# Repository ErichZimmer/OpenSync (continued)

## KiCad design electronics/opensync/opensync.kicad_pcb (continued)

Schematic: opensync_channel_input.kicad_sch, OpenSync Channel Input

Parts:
C65: 100n; C_0402_1005Metric_small_pads; voltage 50V; tolerance ±10%; manufacturer_pn CGA2B3X7R1H104KT0Y0F; LCSC C343042
D1: ESD701DPYR; X1SON-2_L1.0-W0.6-P0.65-BI; MPN ESD701DPYR; LCSC Part C42409125
J17: 705530001; CONN_705530001_02_MOL; LCSC C564143
R81: 1k; R_0402_1005Metric; tolerance ±1%; voltage 50V; manufacturer_pn CRCW04021K00FKEDHP; LCSC C313354
R82: 10k; R_0402_1005Metric; tolerance ±1%; voltage 50V; manufacturer_pn CRCW040210K0FKED; LCSC C71617
U18: TLV3601DCKR; SC-70-5_L2.0-W1.3-P0.65-LS2.1-BR; MPN TLV3601DCKR; LCSC C2974371

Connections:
+3V3: C65.1, U18.5 (VCC); also elsewhere on the board
/Input Channels/Input Channel 1/SIG_LOGIC: U18.3 (IN+); also elsewhere on the board
/Input Channels/SIG_TRIG: U18.1 (OUT); also elsewhere on the board
GND: C65.2, D1.2, J17.2, R81.2, U18.2 (VEE); also elsewhere on the board
unnamed: D1.1, J17.1, R82.2
unnamed: R81.1, R82.1, U18.4 (IN-)

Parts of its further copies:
C66: 100n; C_0402_1005Metric_small_pads; voltage 50V; tolerance ±10%; manufacturer_pn CGA2B3X7R1H104KT0Y0F; LCSC C343042
D11: ESD701DPYR; X1SON-2_L1.0-W0.6-P0.65-BI; MPN ESD701DPYR; LCSC Part C42409125
J18: 705530001; CONN_705530001_02_MOL; LCSC C564143
R83: 1k; R_0402_1005Metric; tolerance ±1%; voltage 50V; manufacturer_pn CRCW04021K00FKEDHP; LCSC C313354
R84: 10k; R_0402_1005Metric; tolerance ±1%; voltage 50V; manufacturer_pn CRCW040210K0FKED; LCSC C71617
U19: TLV3601DCKR; SC-70-5_L2.0-W1.3-P0.65-LS2.1-BR; MPN TLV3601DCKR; LCSC C2974371

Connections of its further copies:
+3V3: C66.1, U19.5 (VCC); also elsewhere on the board
/Input Channels/Input Channel 2/SIG_LOGIC: U19.3 (IN+); also elsewhere on the board
/Input Channels/SIG_GATE: U19.1 (OUT); also elsewhere on the board
GND: C66.2, D11.2, J18.2, R83.2, U19.2 (VEE); also elsewhere on the board
unnamed: D11.1, J18.1, R84.2
unnamed: R83.1, R84.1, U19.4 (IN-)

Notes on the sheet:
NOTE MICROCONTROLLER SCHEM. HAS GPIO PULL DOWNN

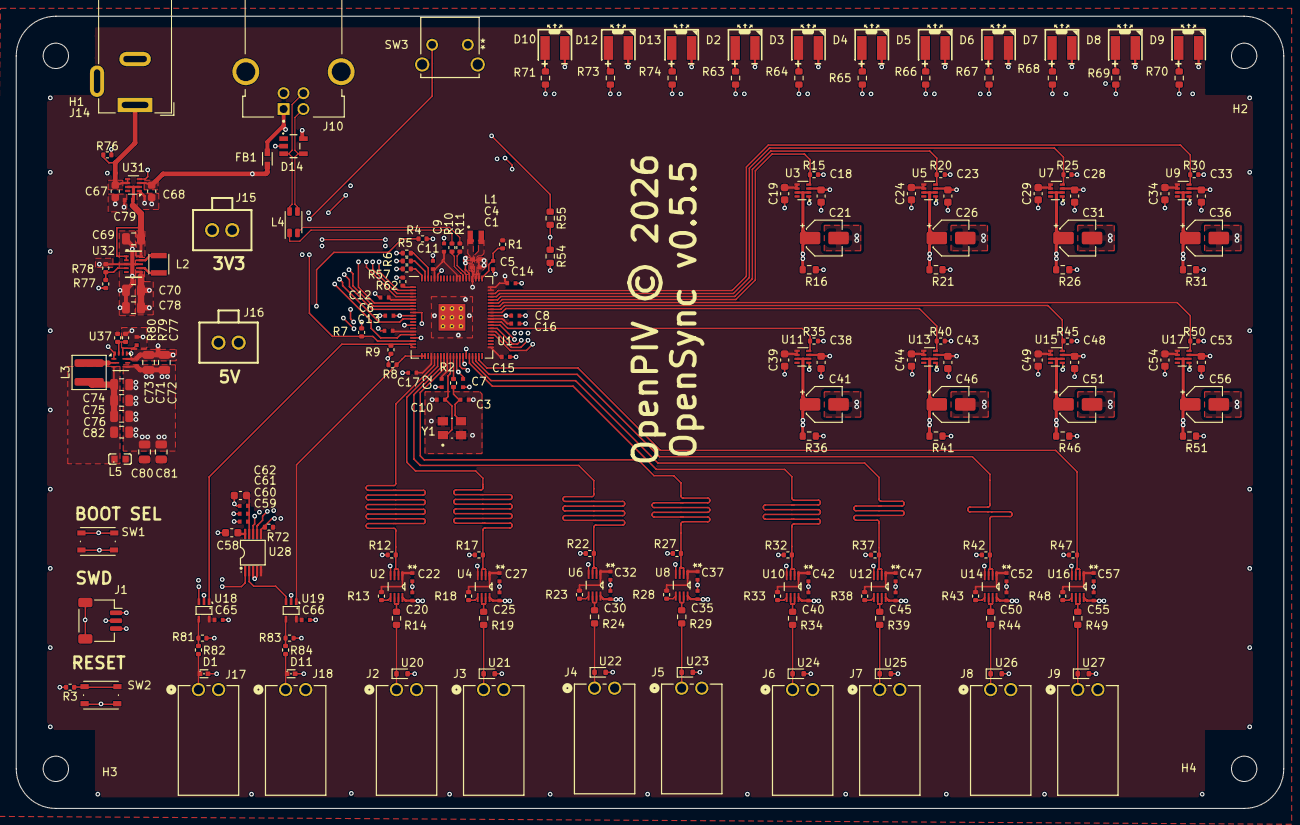
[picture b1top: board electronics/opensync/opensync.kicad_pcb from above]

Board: 4 copper layers, 160.0 x 100.0 mm, 230 parts (0 on the bottom side), 120 nets.

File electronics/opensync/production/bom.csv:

Designator,Footprint,Quantity,Value,LCSC Part #
"C1, C4, C5",0402,3,4.7u,C342983
"C10, C11, C12, C13, C14, C15, C16, C17, C20, C22, C25, C27, C30, C32, C35, C37, C40, C42, C45, C47, C50, C52, C55, C57, C6, C61, C65, C66, C7, C79, C8, C9",0402,32,100n,C343042
"C18, C19, C23, C24, C28, C29, C33, C34, C38, C39, C43, C44, C48, C49, C53, C54, C58, C62, C67, C68",0603,20,1u,C76708
"C2, C3",0402,2,15p,C338103
"C21, C26, C31, C36, C41, C46, C51, C56",CP_Elec_4x5.4,8,22u,C2164097
C59,0402,1,100p,C281750
C60,0402,1,1n,C76704
"C69, C70, C74, C75, C76, C78, C80, C81, C82",0805,9,22u,C342717
"C71, C72",0805,2,10u,C342722
C73,0402,1,2.2n,C338081
C77,0402,1,470n,C432936
"D1, D11",X1SON-2_L1.0-W0.6-P0.65-BI,2,ESD701DPYR,C42409125
"D10, D12, D13, D2, D3, D4, D5, D6, D7, D8, D9",LED-SMD_L4.0-W3.6_A67F-U2BA-1-3A4B-30-R33,11,LED,C7545687
D14,WE-TVS_SOT23-5L,1,5V,C5341668
FB1,FB_Wurth_WE-CBF-0603_W2.6,1,0603_W2.6_742792641,C2649308
J1,JST_SH_SM03B-SRSS-TB_1x03-1MP_P1.00mm_Horizontal,1,SM03B-SRSS-TB,C160403
J10,AMPHENOL_61729-0010BLF,1,61729-0010BLF,C598579
J14,BarrelJack_Wuerth_6941xx301002,1,Barrel_Jack_Switch,C5441017
"J15, J16",CONN-TH_705430001,2,Conn_01x02,C127361
"J17, J18, J2, J3, J4, J5, J6, J7, J8, J9",CONN_705530001_02_MOL,10,705530001,C564143
L1,L_pol_2016,1,3.3u,C42411119
L2,L_TDK_TMS252012ALM,1,470n,C24296304
L3,L_Wuerth_MAPI-4020,1,2.2u,C5521727
L4,L_CommonMode_Wurth_WE-CNSW-1206,1,Choke_Wurth_WE-CNSW_744232090,C2649327
L5,L0603,1,7427922808,C2661810
R1,0402,1,33,C844506
"R10, R11",0402,2,27,C4162575
"R12, R15, R17, R20, R22, R25, R27, R30, R32, R35, R37, R40, R42, R45, R47, R5, R50, R57, R6, R62, R7, R72, R8, R82, R84, R9",0402,26,10k,C71617
"R13, R18, R23, R28, R33, R38, R43, R48",0402,8,47k,C482184
"R14, R19, R24, R29, R34, R39, R44, R49",0603,8,39,C544038
"R16, R21, R26, R31, R36, R41, R46, R51, R54",0603,9,10k,C844918
"R2, R3, R4, R81, R83",0402,5,1k,C313354
R55,0603,1,5.6k,C844799
"R63, R64, R65, R66, R67, R68, R69, R70, R71, R73, R74",0603,11,470,C844786
R76,0402,1,100k,C481918
R77,0402,1,806k,C2076627
R78,0402,1,91k,C2086333
R79,0402,1,4.99k,C4010684
R80,0402,1,15.6k,C2075329
"SW1, SW2",SW_Push_1P1T_NO_Vertical_Wuerth_434133025816,2,SW_Push,C5504987
SW3,SW2_1825027-G_TEC,1,2-1825027-0,C590206
U1,RP2350-QFN-80-1EP_10x10_P0.4mm_EP3.4x3.4mm_ThermalVias,1,RP2354_80QFN,C39843328
"U10, U12, U14, U16, U2, U4, U6, U8",DCU8,8,SN74LVC2T45DCUR,C15741
"U11, U13, U15, U17, U3, U31, U5, U7, U9",SOT-583-8,9,TPS2116DRL,C3235557
"U18, U19",SC-70-5_L2.0-W1.3-P0.65-LS2.1-BR,2,TLV3601DCKR,C2974371
"U20, U21, U22, U23, U24, U25, U26, U27",D_SOD-523,8,TPD1E05U06DYA,C3702980
U28,VSSOP-10_L3.0-W3.0-P0.50-LS4.9-BL,1,DAC8563SDGSR,C1554729
U32,DLA0010A,1,TPS63802DLAR,C2845237
U37,Texas_RPU0010A_VQFN-HR-10_2x2mm_P0.5mm,1,TPS62912,C3198056
Y1,XTAL_ABM8-272-T3,1,ABM8-272-T3,C20625731

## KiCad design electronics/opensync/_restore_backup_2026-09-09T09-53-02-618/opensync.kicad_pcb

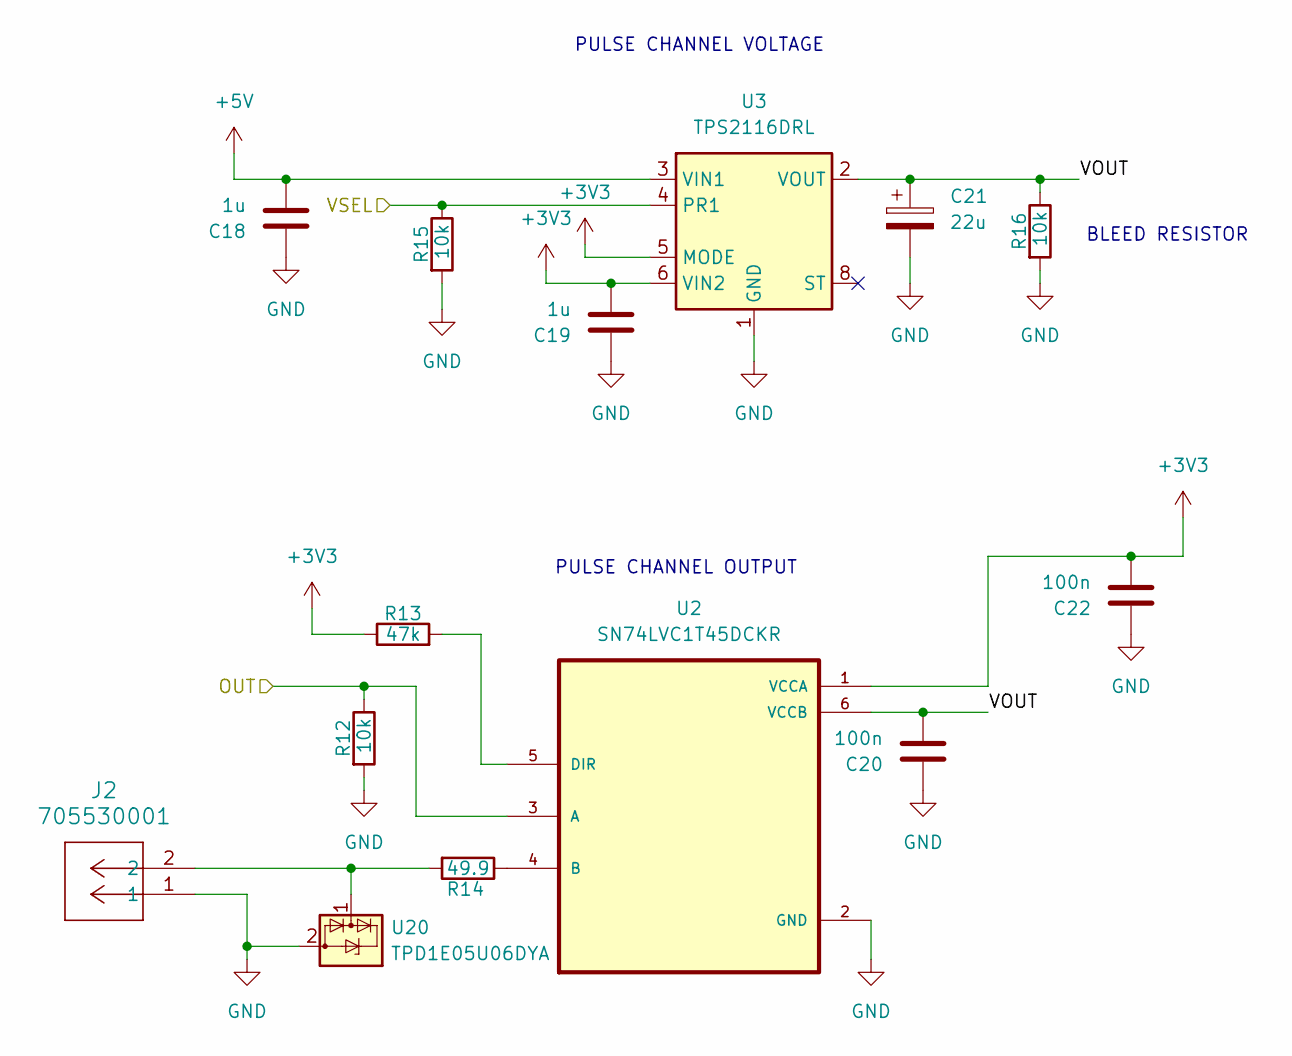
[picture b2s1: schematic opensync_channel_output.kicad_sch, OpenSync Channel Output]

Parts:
C18, C19: 1u; C_0402_1005Metric_small_pads
C20, C22: 100n; C_0402_1005Metric_small_pads; LCSC C60474
C21: 22u; CP_Elec_4x5.4
J2: 705530001; CONN_705530001_02_MOL; LCSC C564143
R12, R15: 10k; R_0402_1005Metric; LCSC C71617
R13: 47k; R_0402_1005Metric; LCSC C176117
R14: 49.9; R_0603_1608Metric; LCSC C1858992
R16: 10k; R_0402_1005Metric
U2: SN74LVC1T45DCKR; SOT65P210X110-6N; LCSC C9382
U3: TPS2116DRL; SOT-583-8
U20: TPD1E05U06DYA; D_SOD-523

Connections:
+3V3: C19.2, C22.2, R13.1, U2.1 (VCCA), U3.5 (MODE), U3.6 (VIN2); also elsewhere on the board
+5V: C18.2, U3.3 (VIN1); also elsewhere on the board
/OUT_A: R12.1, U2.3 (A); also elsewhere on the board
/Output Channel 1/VOUT: C20.2, C21.1, R16.1, U2.6 (VCCB), U3.2 (VOUT), U3.7 (VOUT)
/VSEL_A: R15.1, U3.4 (PR1); also elsewhere on the board
GND: C18.1, C19.1, C20.1, C21.2, C22.1, J2.1, R12.2, R15.2, R16.2, U2.2 (GND), U3.1 (GND), U20.2 (GND); also elsewhere on the board
unnamed: R14.1, U2.4 (B)
unnamed: R13.2, U2.5 (DIR)
unnamed: J2.2, R14.2, U20.1 (I/O)

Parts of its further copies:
C23, C24, C28, C29, C33, C34, C38, C39, C43, C44, C48, C49, C53, C54, C58, C59: 1u; C_0402_1005Metric_small_pads
C25, C27, C30, C32, C35, C37, C40, C42, C45, C47, C50, C52, C55, C57, C60, C62: 100n; C_0402_1005Metric_small_pads; LCSC C60474
C26, C31, C36, C41, C46, C51, C56, C61: 22u; CP_Elec_4x5.4
J3, J4, J5, J6, J7, J8, J9, J10: 705530001; CONN_705530001_02_MOL; LCSC C564143
R17, R20, R22, R25, R27, R30, R32, R35, R37, R40, R42, R45, R47, R50, R52, R55: 10k; R_0402_1005Metric; LCSC C71617
R18, R23, R28, R33, R38, R43, R48, R53: 47k; R_0402_1005Metric; LCSC C176117
R19, R24, R29, R34, R39, R44, R49, R54: 49.9; R_0603_1608Metric; LCSC C1858992
R21, R26, R31, R36, R41, R46, R51, R56: 10k; R_0402_1005Metric
U4, U6, U8, U10, U12, U14, U16, U18: SN74LVC1T45DCKR; SOT65P210X110-6N; LCSC C9382
U5, U7, U9, U11, U13, U15, U17, U19: TPS2116DRL; SOT-583-8
U21, U22, U23, U24, U25, U26, U27, U28: TPD1E05U06DYA; D_SOD-523

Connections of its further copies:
+3V3: C24.2, C27.2, C29.2, C32.2, C34.2, C37.2, C39.2, C42.2, C44.2, C47.2, C49.2, C52.2, C54.2, C57.2, C59.2, C62.2, R18.1, R23.1, R28.1, R33.1, R38.1, R43.1, R48.1, R53.1, U4.1 (VCCA), U5.5 (MODE), U5.6 (VIN2), U6.1 (VCCA), U7.5 (MODE), U7.6 (VIN2), U8.1 (VCCA), U9.5 (MODE), U9.6 (VIN2), U10.1 (VCCA), U11.5 (MODE), U11.6 (VIN2), U12.1 (VCCA), U13.5 (MODE), U13.6 (VIN2), U14.1 (VCCA), U15.5 (MODE), U15.6 (VIN2), U16.1 (VCCA), U17.5 (MODE), U17.6 (VIN2), U18.1 (VCCA), U19.5 (MODE), U19.6 (VIN2); also elsewhere on the board
+5V: C23.2, C28.2, C33.2, C38.2, C43.2, C48.2, C53.2, C58.2, U5.3 (VIN1), U7.3 (VIN1), U9.3 (VIN1), U11.3 (VIN1), U13.3 (VIN1), U15.3 (VIN1), U17.3 (VIN1), U19.3 (VIN1); also elsewhere on the board
/OUT_B: R17.1, U4.3 (A); also elsewhere on the board
/OUT_C: R22.1, U6.3 (A); also elsewhere on the board
/OUT_D: R27.1, U8.3 (A); also elsewhere on the board
/OUT_E: R32.1, U10.3 (A); also elsewhere on the board
/OUT_F: R37.1, U12.3 (A); also elsewhere on the board
/OUT_G: R42.1, U14.3 (A); also elsewhere on the board
/OUT_H: R47.1, U16.3 (A); also elsewhere on the board
/OUT_T0: R52.1, U18.3 (A); also elsewhere on the board
/Output Channel 2/VOUT: C25.2, C26.1, R21.1, U4.6 (VCCB), U5.2 (VOUT), U5.7 (VOUT)
/Output Channel 3/VOUT: C30.2, C31.1, R26.1, U6.6 (VCCB), U7.2 (VOUT), U7.7 (VOUT)
/Output Channel 4/VOUT: C35.2, C36.1, R31.1, U8.6 (VCCB), U9.2 (VOUT), U9.7 (VOUT)
/Output Channel 5/VOUT: C40.2, C41.1, R36.1, U10.6 (VCCB), U11.2 (VOUT), U11.7 (VOUT)
/Output Channel 6/VOUT: C45.2, C46.1, R41.1, U12.6 (VCCB), U13.2 (VOUT), U13.7 (VOUT)
/Output Channel 7/VOUT: C50.2, C51.1, R46.1, U14.6 (VCCB), U15.2 (VOUT), U15.7 (VOUT)
/Output Channel 8/VOUT: C55.2, C56.1, R51.1, U16.6 (VCCB), U17.2 (VOUT), U17.7 (VOUT)
/Output Channel T0/VOUT: C60.2, C61.1, R56.1, U18.6 (VCCB), U19.2 (VOUT), U19.7 (VOUT)
/VSEL_B: R20.1, U5.4 (PR1); also elsewhere on the board
/VSEL_C: R25.1, U7.4 (PR1); also elsewhere on the board
/VSEL_D: R30.1, U9.4 (PR1); also elsewhere on the board
/VSEL_E: R35.1, U11.4 (PR1); also elsewhere on the board
/VSEL_F: R40.1, U13.4 (PR1); also elsewhere on the board
/VSEL_G: R45.1, U15.4 (PR1); also elsewhere on the board
/VSEL_H: R50.1, U17.4 (PR1); also elsewhere on the board
/VSEL_T0: R55.1, U19.4 (PR1); also elsewhere on the board
GND: C23.1, C24.1, C25.1, C26.2, C27.1, C28.1, C29.1, C30.1, C31.2, C32.1, C33.1, C34.1, C35.1, C36.2, C37.1, C38.1, C39.1, C40.1, C41.2, C42.1, C43.1, C44.1, C45.1, C46.2, C47.1, C48.1, C49.1, C50.1, C51.2, C52.1, C53.1, C54.1, C55.1, C56.2, C57.1, C58.1, C59.1, C60.1, C61.2, C62.1, J3.1, J4.1, J5.1, J6.1, J7.1, J8.1, J9.1, J10.1, R17.2, R20.2, R21.2, R22.2, R25.2, R26.2, R27.2, R30.2, R31.2, R32.2, R35.2, R36.2, R37.2, R40.2, R41.2, R42.2, R45.2, R46.2, R47.2, R50.2, R51.2, R52.2, R55.2, R56.2, U4.2 (GND), U5.1 (GND), U6.2 (GND), U7.1 (GND), U8.2 (GND), U9.1 (GND), U10.2 (GND), U11.1 (GND), U12.2 (GND), U13.1 (GND), U14.2 (GND), U15.1 (GND), U16.2 (GND), U17.1 (GND), U18.2 (GND), U19.1 (GND), U21.2 (GND), U22.2 (GND), U23.2 (GND), U24.2 (GND), U25.2 (GND), U26.2 (GND), U27.2 (GND), U28.2 (GND); also elsewhere on the board
unnamed: R19.1, U4.4 (B)
unnamed: R18.2, U4.5 (DIR)
unnamed: R24.1, U6.4 (B)
unnamed: R23.2, U6.5 (DIR)
unnamed: R29.1, U8.4 (B)
unnamed: R28.2, U8.5 (DIR)
unnamed: R34.1, U10.4 (B)
unnamed: R33.2, U10.5 (DIR)
unnamed: R39.1, U12.4 (B)
unnamed: R38.2, U12.5 (DIR)
unnamed: R44.1, U14.4 (B)
unnamed: R43.2, U14.5 (DIR)
unnamed: R49.1, U16.4 (B)
unnamed: R48.2, U16.5 (DIR)
unnamed: R54.1, U18.4 (B)
unnamed: R53.2, U18.5 (DIR)
unnamed: J3.2, R19.2, U21.1 (I/O)
unnamed: J4.2, R24.2, U22.1 (I/O)
unnamed: J5.2, R29.2, U23.1 (I/O)
unnamed: J6.2, R34.2, U24.1 (I/O)
unnamed: J7.2, R39.2, U25.1 (I/O)
unnamed: J8.2, R44.2, U26.1 (I/O)
unnamed: J9.2, R49.2, U27.1 (I/O)
unnamed: J10.2, R54.2, U28.1 (I/O)

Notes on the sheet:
BLEED RESISTOR
PULSE CHANNEL OUTPUT
PULSE CHANNEL VOLTAGE

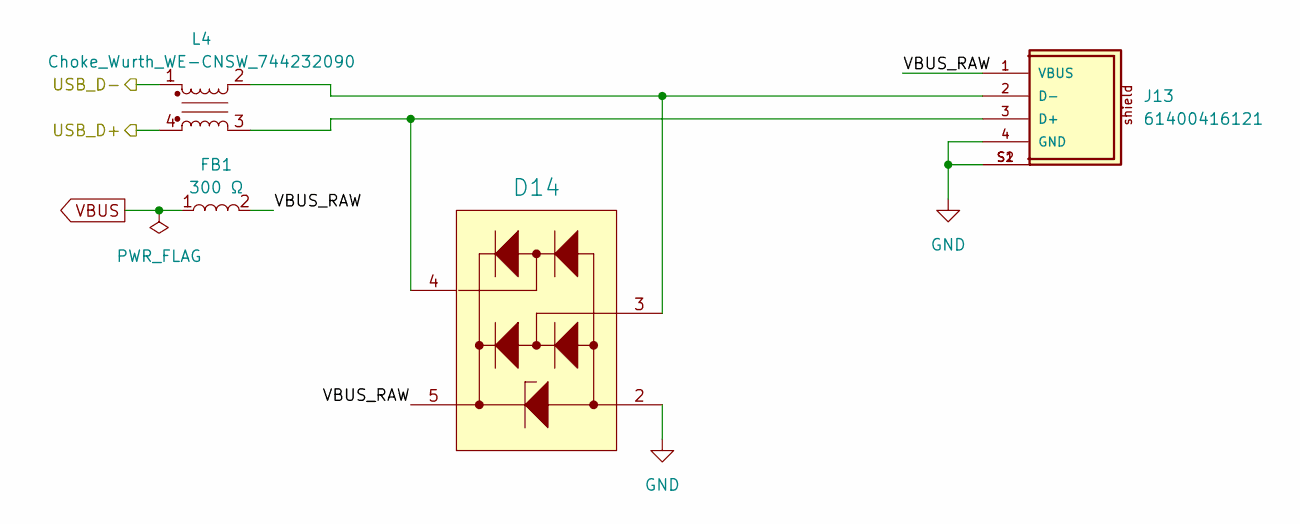
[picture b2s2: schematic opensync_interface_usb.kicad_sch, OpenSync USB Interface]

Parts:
D14: 5V; WE-TVS_SOT563; Manufacturer Part Number 824011
FB1: 0603_W2.6_742792641; FB_Wurth_WE-CBF-0603_W2.6; Part Number 742792641
J13: 61400416121
L4: Choke_Wurth_WE-CNSW_744232090; L_CommonMode_Wurth_WE-CNSW-1206

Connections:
/Microcontroller Circuitry/USB_D+: D14.4 (I/O_2), J13.3 (D+), L4.3; also elsewhere on the board
/Microcontroller Circuitry/USB_D-: D14.3 (I/O_1), J13.2 (D-), L4.2; also elsewhere on the board
GND: D14.2 (GND), J13.4 (GND), J13.S1, J13.S2; also elsewhere on the board
VBUS: D14.5 (VDD), FB1.2, J13.1 (VBUS); also elsewhere on the board

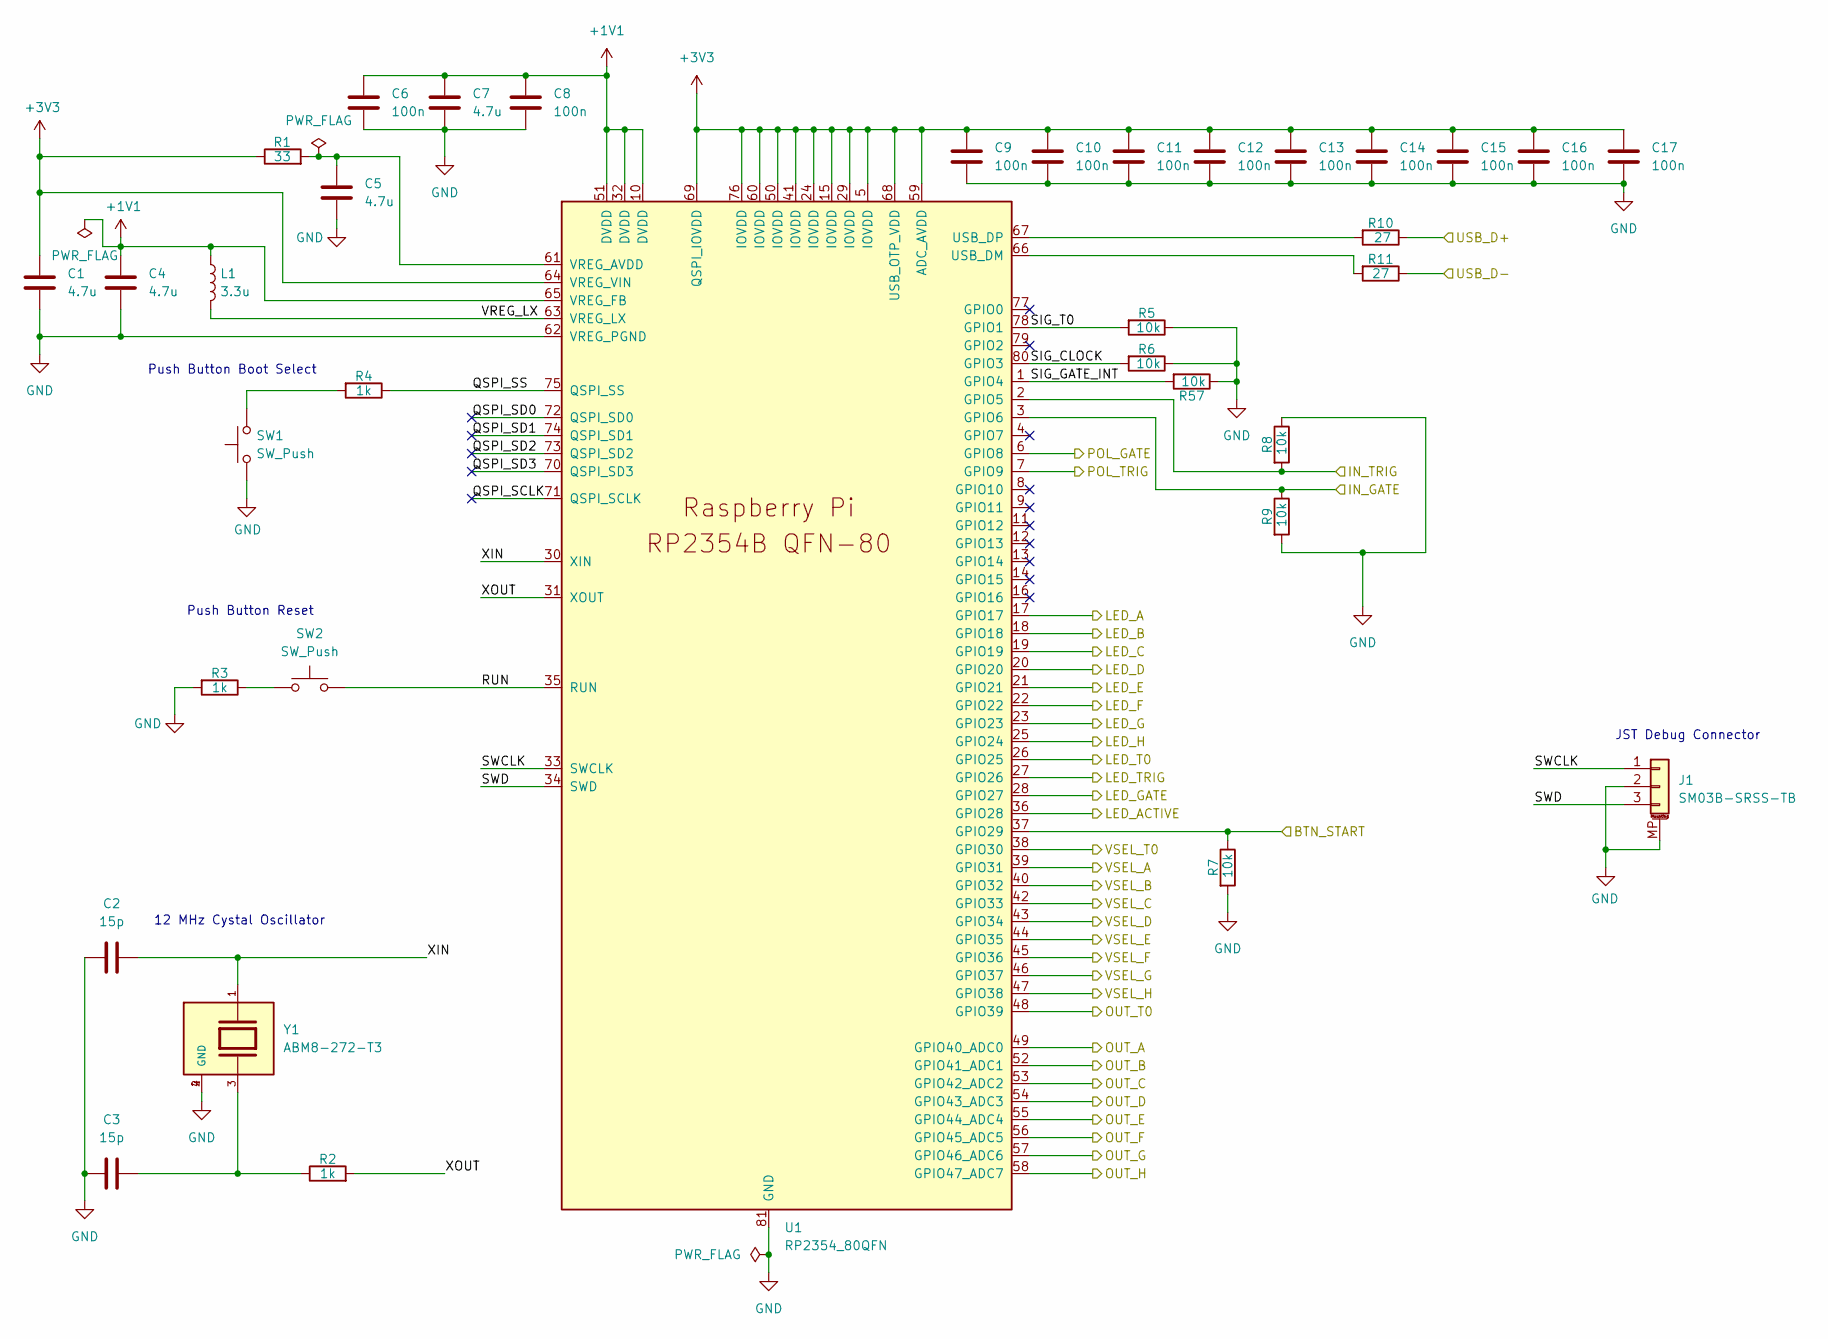
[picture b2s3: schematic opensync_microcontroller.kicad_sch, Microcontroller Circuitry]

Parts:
C1, C4, C5: 4.7u; C_0402_1005Metric_small_pads; LCSC C326586
C2, C3: 15p; C_0402_1005Metric_small_pads; LCSC C326803
C6, C8, C9, C10, C11, C12, C13, C14, C15, C16, C17: 100n; C_0402_1005Metric_small_pads; LCSC C60474
C7: 4.7u; C_0402_1005Metric_small_pads; LCSC C60474
J1: SM03B-SRSS-TB; JST_SH_SM03B-SRSS-TB_1x03-1MP_P1.00mm_Horizontal; LCSC C160403
L1: 3.3u; L_pol_2016; LCSC C42411119
R1: 33; R_0402_1005Metric; LCSC C844506
R2, R3, R4: 1k; R_0402_1005Metric; LCSC C313354
R5, R6, R7, R8, R9, R57: 10k; R_0402_1005Metric; LCSC C71617
R10, R11: 27; R_0402_1005Metric; LCSC C4162575
SW1, SW2: SW_Push; SW_Push_1P1T_NO_Vertical_Wuerth_434133025816; LCSC C5504987
U1: RP2354_80QFN; RP2350-QFN-80-1EP_10x10_P0.4mm_EP3.4x3.4mm_ThermalVias
Y1: ABM8-272-T3; XTAL_ABM8-272-T3; PARTREV 07-29-20

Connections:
+1V1: C4.1, C6.1, C7.1, C8.1, L1.1, U1.10 (DVDD), U1.32 (DVDD), U1.51 (DVDD), U1.65 (VREG_FB)
+3V3: C1.1, C9.1, C10.1, C11.1, C12.1, C13.1, C14.1, C15.1, C16.1, C17.1, R1.1, U1.5 (IOVDD), U1.15 (IOVDD), U1.24 (IOVDD), U1.29 (IOVDD), U1.41 (IOVDD), U1.50 (IOVDD), U1.59 (ADC_AVDD), U1.60 (IOVDD), U1.64 (VREG_VIN), U1.68 (USB_OTP_VDD), U1.69 (QSPI_IOVDD), U1.76 (IOVDD); also elsewhere on the board
/IN_G: R9.1, U1.3 (GPIO6); also elsewhere on the board
/IN_T: R8.2, U1.2 (GPIO5); also elsewhere on the board
/ISEL_G: U1.6 (GPIO8); also elsewhere on the board
/ISEL_T: U1.7 (GPIO9); also elsewhere on the board
/Indicator Panel/BTN_START: R7.1, U1.37 (GPIO29); also elsewhere on the board
/Indicator Panel/LED_A: U1.17 (GPIO17); also elsewhere on the board
/Indicator Panel/LED_ACTIVE: U1.36 (GPIO28); also elsewhere on the board
/Indicator Panel/LED_B: U1.18 (GPIO18); also elsewhere on the board
/Indicator Panel/LED_C: U1.19 (GPIO19); also elsewhere on the board
/Indicator Panel/LED_D: U1.20 (GPIO20); also elsewhere on the board
/Indicator Panel/LED_E: U1.21 (GPIO21); also elsewhere on the board
/Indicator Panel/LED_F: U1.22 (GPIO22); also elsewhere on the board
/Indicator Panel/LED_G: U1.23 (GPIO23); also elsewhere on the board
/Indicator Panel/LED_GATE: U1.28 (GPIO27); also elsewhere on the board
/Indicator Panel/LED_H: U1.25 (GPIO24); also elsewhere on the board
/Indicator Panel/LED_T0: U1.26 (GPIO25); also elsewhere on the board
/Indicator Panel/LED_TRIG: U1.27 (GPIO26); also elsewhere on the board
/Microcontroller Circuitry/QSPI_SCLK: U1.71 (QSPI_SCLK)
/Microcontroller Circuitry/QSPI_SD0: U1.72 (QSPI_SD0)
/Microcontroller Circuitry/QSPI_SD1: U1.74 (QSPI_SD1)
/Microcontroller Circuitry/QSPI_SD2: U1.73 (QSPI_SD2)
/Microcontroller Circuitry/QSPI_SD3: U1.70 (QSPI_SD3)
/Microcontroller Circuitry/QSPI_SS: R4.1, U1.75 (QSPI_SS)
/Microcontroller Circuitry/RUN: SW2.2, U1.35 (RUN)
/Microcontroller Circuitry/SIG_CLOCK: R6.2, U1.80 (GPIO3)
/Microcontroller Circuitry/SIG_GATE_INT: R57.2, U1.1 (GPIO4)
/Microcontroller Circuitry/SIG_T0: R5.2, U1.78 (GPIO1)
/Microcontroller Circuitry/SWCLK: J1.1, U1.33 (SWCLK)
/Microcontroller Circuitry/SWD: J1.3, U1.34 (SWD)
/Microcontroller Circuitry/USB_D+: R10.1; also elsewhere on the board
/Microcontroller Circuitry/USB_D-: R11.1; also elsewhere on the board
/Microcontroller Circuitry/VREG_LX: L1.2, U1.63 (VREG_LX)
/Microcontroller Circuitry/XIN: C2.2, U1.30 (XIN), Y1.1
/Microcontroller Circuitry/XOUT: R2.2, U1.31 (XOUT)
/OUT_A: U1.49 (GPIO40_ADC0); also elsewhere on the board
/OUT_B: U1.52 (GPIO41_ADC1); also elsewhere on the board
/OUT_C: U1.53 (GPIO42_ADC2); also elsewhere on the board
/OUT_D: U1.54 (GPIO43_ADC3); also elsewhere on the board
/OUT_E: U1.55 (GPIO44_ADC4); also elsewhere on the board
/OUT_F: U1.56 (GPIO45_ADC5); also elsewhere on the board
/OUT_G: U1.57 (GPIO46_ADC6); also elsewhere on the board
/OUT_H: U1.58 (GPIO47_ADC7); also elsewhere on the board
/OUT_T0: U1.48 (GPIO39); also elsewhere on the board
/VSEL_A: U1.39 (GPIO31); also elsewhere on the board
/VSEL_B: U1.40 (GPIO32); also elsewhere on the board
/VSEL_C: U1.42 (GPIO33); also elsewhere on the board
/VSEL_D: U1.43 (GPIO34); also elsewhere on the board
/VSEL_E: U1.44 (GPIO35); also elsewhere on the board
/VSEL_F: U1.45 (GPIO36); also elsewhere on the board
/VSEL_G: U1.46 (GPIO37); also elsewhere on the board
/VSEL_H: U1.47 (GPIO38); also elsewhere on the board
/VSEL_T0: U1.38 (GPIO30); also elsewhere on the board
GND: C1.2, C2.1, C3.1, C4.2, C5.2, C6.2, C7.2, C8.2, C9.2, C10.2, C11.2, C12.2, C13.2, C14.2, C15.2, C16.2, C17.2, J1.2, J1.MP (MountPin), R3.2, R5.1, R6.1, R7.2, R8.1, R9.2, R57.1, SW1.1, U1.62 (VREG_PGND), U1.81 (GND), Y1.2 (GND), Y1.4 (GND); also elsewhere on the board
unnamed: C3.2, R2.1, Y1.3
unnamed: R3.1, SW2.1
unnamed: R4.2, SW1.2
unnamed: R11.2, U1.66 (USB_DM)
unnamed: R10.2, U1.67 (USB_DP)
unnamed: C5.1, R1.2, U1.61 (VREG_AVDD)

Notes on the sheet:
Push Button Boot Select
JST Debug Connector
12 MHz Cystal Oscillator
Push Button Reset

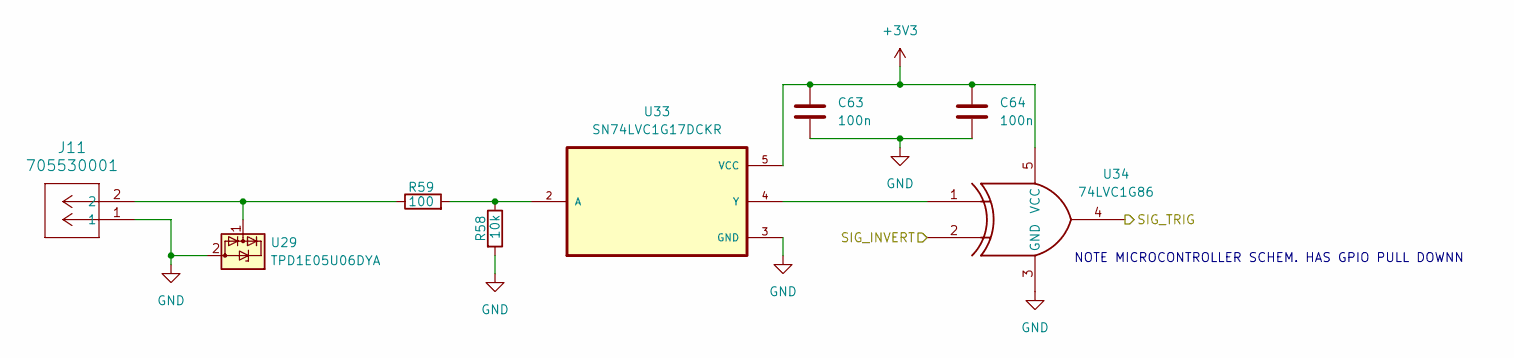
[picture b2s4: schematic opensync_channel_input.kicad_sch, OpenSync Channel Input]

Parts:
C63, C64: 100n; C_0402_1005Metric_small_pads; LCSC C60474
J11: 705530001; CONN_705530001_02_MOL
R58: 10k; R_0402_1005Metric; LCSC C71617
R59: 100; R_0402_1005Metric
U29: TPD1E05U06DYA; D_SOD-523
U33: SN74LVC1G17DCKR; SOT65P210X110-5N; DigiKey_Part_Number 296-11934-1-ND
U34: 74LVC1G86; SOT65P210X110-5N

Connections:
+3V3: C63.1, C64.1, U33.5 (VCC), U34.5 (VCC); also elsewhere on the board
/IN_T: U34.4; also elsewhere on the board
/ISEL_T: U34.2; also elsewhere on the board
GND: C63.2, C64.2, J11.1, R58.2, U29.2 (GND), U33.3 (GND), U34.3 (GND); also elsewhere on the board
unnamed: J11.2, R59.1, U29.1 (I/O)
unnamed: R58.1, R59.2, U33.2 (A)
unnamed: U33.4 (Y), U34.1

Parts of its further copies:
C65, C66: 100n; C_0402_1005Metric_small_pads; LCSC C60474
J12: 705530001; CONN_705530001_02_MOL
R60: 100; R_0402_1005Metric
R61: 10k; R_0402_1005Metric; LCSC C71617
U30: TPD1E05U06DYA; D_SOD-523
U35: SN74LVC1G17DCKR; SOT65P210X110-5N; DigiKey_Part_Number 296-11934-1-ND
U36: 74LVC1G86; SOT65P210X110-5N

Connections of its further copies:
+3V3: C65.1, C66.1, U35.5 (VCC), U36.5 (VCC); also elsewhere on the board
/IN_G: U36.4; also elsewhere on the board
/ISEL_G: U36.2; also elsewhere on the board
GND: C65.2, C66.2, J12.1, R61.2, U30.2 (GND), U35.3 (GND), U36.3 (GND); also elsewhere on the board
unnamed: J12.2, R60.1, U30.1 (I/O)
unnamed: R60.2, R61.1, U35.2 (A)
unnamed: U35.4 (Y), U36.1

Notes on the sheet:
NOTE MICROCONTROLLER SCHEM. HAS GPIO PULL DOWNN

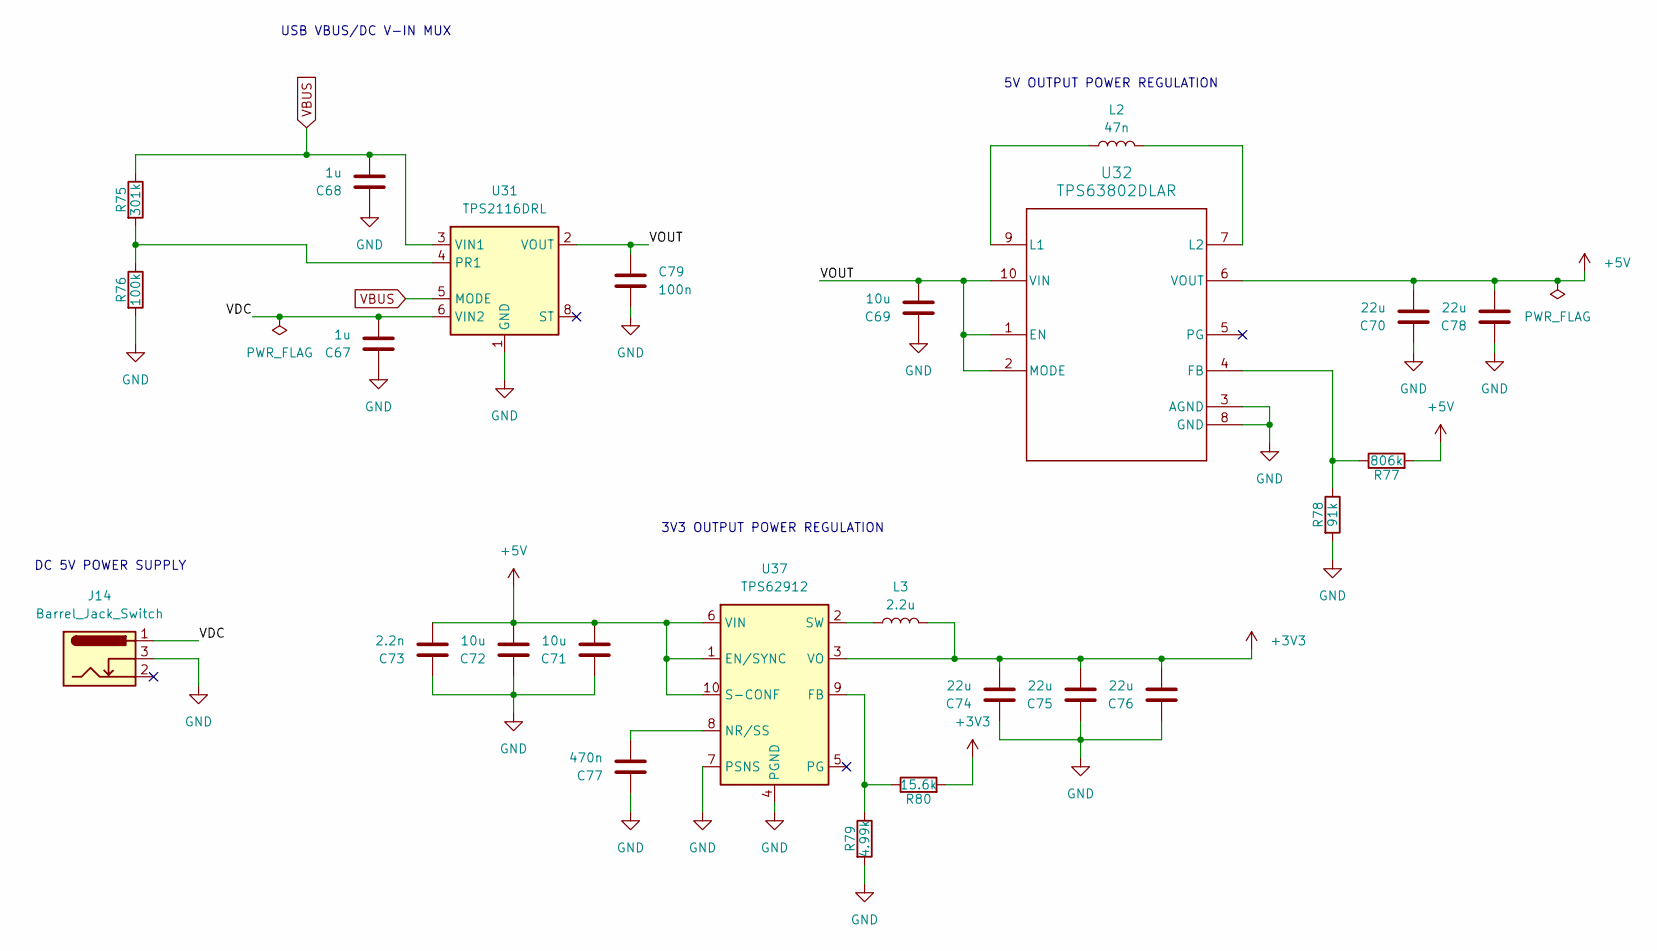
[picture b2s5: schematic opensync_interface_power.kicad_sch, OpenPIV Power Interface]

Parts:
C67, C68: 1u; C_0805_2012Metric
C69, C71, C72: 10u; C_0805_2012Metric
C70, C74, C75, C76, C78: 22u; C_0805_2012Metric
C73: 2.2n; C_0402_1005Metric_small_pads
C77: 470n; C_0402_1005Metric_small_pads
C79: 100n; C_0402_1005Metric_small_pads; LCSC C60474
J14: Barrel_Jack_Switch; BarrelJack_Wuerth_6941xx301002
L2: 47n; L_Wuerth_MAPI-3020; LCSC C2045146
L3: 2.2u; L_Wuerth_MAPI-4020; LCSC C5521727
R75: 301k; R_0402_1005Metric
R76: 100k; R_0402_1005Metric
R77: 806k; R_0402_1005Metric
R78: 91k; R_0402_1005Metric
R79: 4.99k; R_0402_1005Metric
R80: 15.6k; R_0402_1005Metric
U31: TPS2116DRL; SOT-583-8
U32: TPS63802DLAR; DLA0010A
U37: TPS62912; Texas_RPU0010A_VQFN-HR-10_2x2mm_P0.5mm

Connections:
+3V3: C74.2, C75.2, C76.2, L3.2, R80.2, U37.3 (VO); also elsewhere on the board
+5V: C70.2, C71.2, C72.2, C73.2, C78.2, R77.2, U32.6 (VOUT), U37.1 (EN/SYNC), U37.6 (VIN), U37.10 (S-CONF); also elsewhere on the board
/Power Interface/VDC: C67.2, J14.1, U31.6 (VIN2)
/Power Interface/VOUT: C69.2, C79.1, U31.2 (VOUT), U31.7 (VOUT), U32.1 (EN), U32.2 (MODE), U32.10 (VIN)
GND: C67.1, C68.1, C69.1, C70.1, C71.1, C72.1, C73.1, C74.1, C75.1, C76.1, C77.1, C78.1, C79.2, J14.3, R76.2, R78.2, R79.2, U31.1 (GND), U32.3 (AGND), U32.8 (GND), U37.4 (PGND), U37.7 (PSNS); also elsewhere on the board
unnamed: R75.2, R76.1, U31.4 (PR1)
unnamed: R77.1, R78.1, U32.4 (FB)
unnamed: L2.1, U32.9 (L1)
unnamed: L2.2, U32.7 (L2)
unnamed: R79.1, R80.1, U37.9 (FB)
unnamed: C77.2, U37.8 (NR/SS)
unnamed: L3.1, U37.2 (SW)
VBUS: C68.2, R75.1, U31.3 (VIN1), U31.5 (MODE); also elsewhere on the board

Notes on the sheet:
3V3 OUTPUT POWER REGULATION
DC 5V POWER SUPPLY
USB VBUS/DC V-IN MUX
5V OUTPUT POWER REGULATION

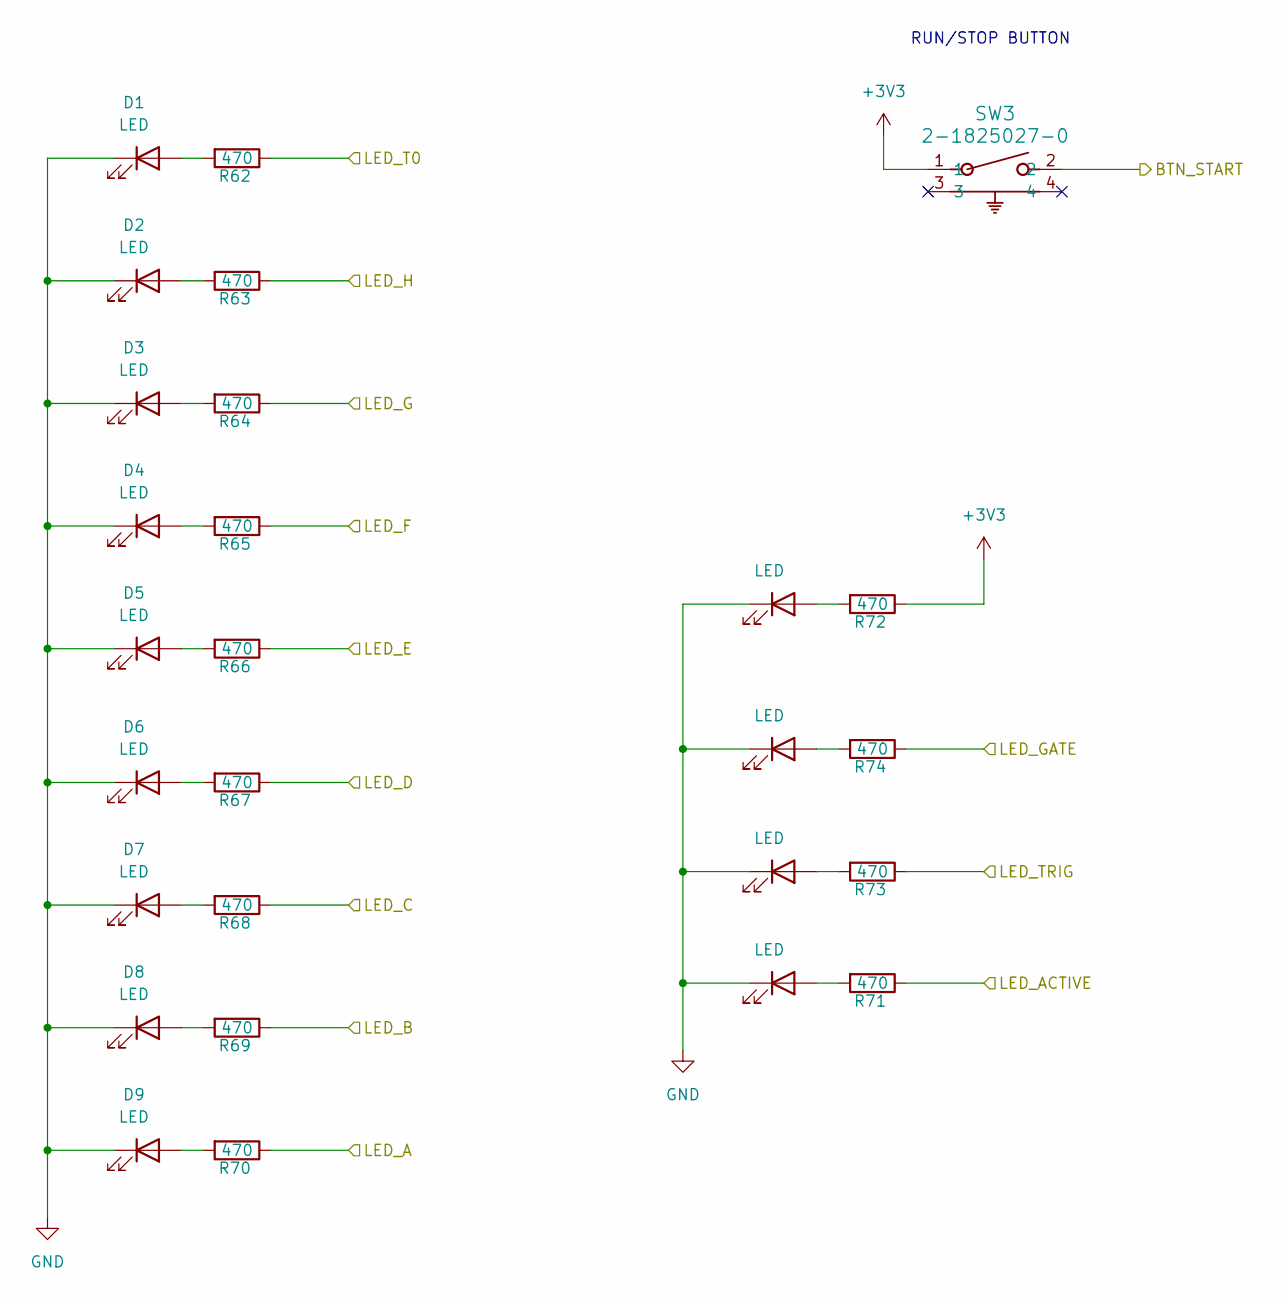
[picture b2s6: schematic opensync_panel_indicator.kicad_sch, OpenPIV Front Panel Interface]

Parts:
D1, D2, D3, D4, D5, D6, D7, D8, D9, D10, D11, D12, D13: LED; LED-SMD_L4.0-W3.6_A67F-U2BA-1-3A4B-30-R33
R62, R63, R64, R65, R66, R67, R68, R69, R70, R71, R72, R73, R74: 470; R_0402_1005Metric
SW3: 2-1825027-0; SW2_1825027-G_TEC

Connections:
+3V3: R72.1, SW3.1; also elsewhere on the board
/Indicator Panel/BTN_START: SW3.2; also elsewhere on the board
/Indicator Panel/LED_A: R70.1; also elsewhere on the board
/Indicator Panel/LED_ACTIVE: R71.1; also elsewhere on the board
/Indicator Panel/LED_B: R69.1; also elsewhere on the board
/Indicator Panel/LED_C: R68.1; also elsewhere on the board
/Indicator Panel/LED_D: R67.1; also elsewhere on the board
/Indicator Panel/LED_E: R66.1; also elsewhere on the board
/Indicator Panel/LED_F: R65.1; also elsewhere on the board
/Indicator Panel/LED_G: R64.1; also elsewhere on the board
/Indicator Panel/LED_GATE: R74.1; also elsewhere on the board
/Indicator Panel/LED_H: R63.1; also elsewhere on the board
/Indicator Panel/LED_T0: R62.1; also elsewhere on the board
/Indicator Panel/LED_TRIG: R73.1; also elsewhere on the board
GND: D1.1 (K), D2.1 (K), D3.1 (K), D4.1 (K), D5.1 (K), D6.1 (K), D7.1 (K), D8.1 (K), D9.1 (K), D10.1 (K), D11.1 (K), D12.1 (K), D13.1 (K); also elsewhere on the board
unnamed: D1.2 (A), R62.2
unnamed: D2.2 (A), R63.2
unnamed: D3.2 (A), R64.2
unnamed: D4.2 (A), R65.2
unnamed: D5.2 (A), R66.2
unnamed: D6.2 (A), R67.2
unnamed: D7.2 (A), R68.2
unnamed: D8.2 (A), R69.2
unnamed: D9.2 (A), R70.2
unnamed: D10.2 (A), R71.2
unnamed: D11.2 (A), R72.2
unnamed: D12.2 (A), R73.2
unnamed: D13.2 (A), R74.2

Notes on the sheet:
RUN/STOP BUTTON

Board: 2 copper layers, 230 parts (0 on the bottom side), 122 nets, no tracks yet.

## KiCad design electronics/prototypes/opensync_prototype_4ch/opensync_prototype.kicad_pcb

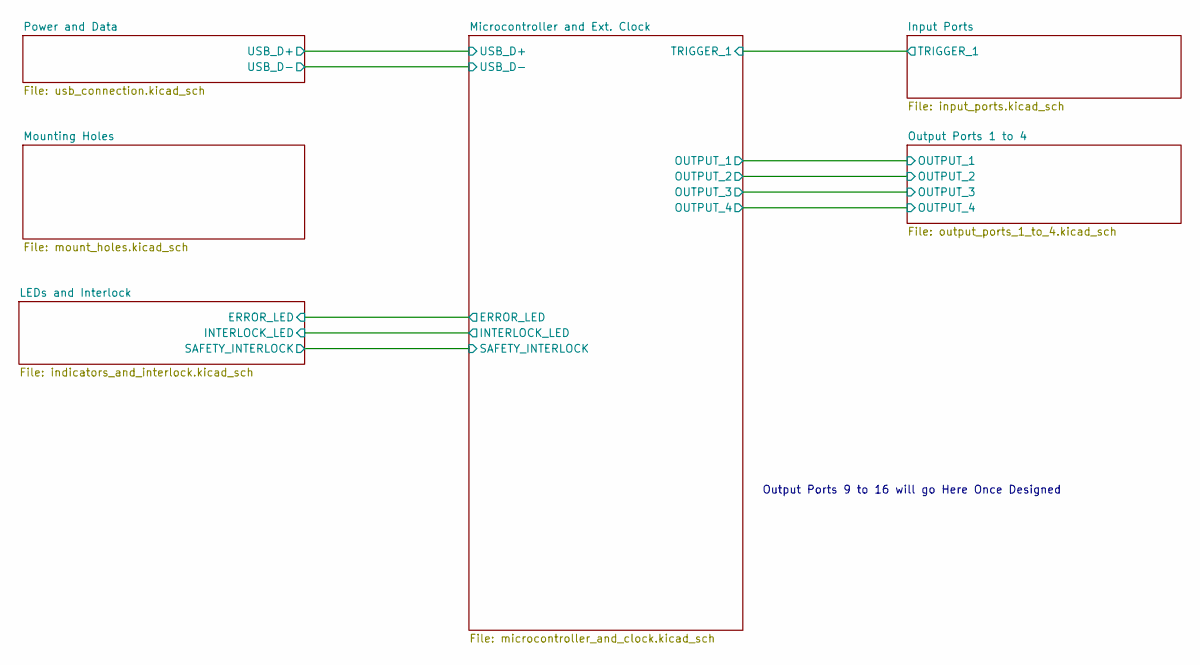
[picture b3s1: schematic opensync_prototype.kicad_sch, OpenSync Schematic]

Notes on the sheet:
Output Ports 9 to 16 will go Here Once Designed
